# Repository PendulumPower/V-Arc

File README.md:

# V-ARC (WIP)
V-ARC is a multi-effects pedal, preamp, ble page turner, and looper designed for electric violin. It can also be used for other electric
instruments such as guitar. It runs on 2 separate controllers and includes a Lipo battery. It will be capable of being wirelessly reprogrammed for convienience,
and should have an app later in development so that settings can be tweaked or effects swapped without interacting with it. It is also going to feature MIDI conversion
and wireless playback in the future.
<br>Images:
<br>Schematic:

<br>PCB:

<br>Cost Breakdown:
<br>-Digikey components+Tax+Tariff+Shipping: ~$80
<br>Dasiy seed3+Tax+Shipping: ~$40
<br>PCB+Stencil+Tax+Shipping: ~$35
<br>Total: ~$155

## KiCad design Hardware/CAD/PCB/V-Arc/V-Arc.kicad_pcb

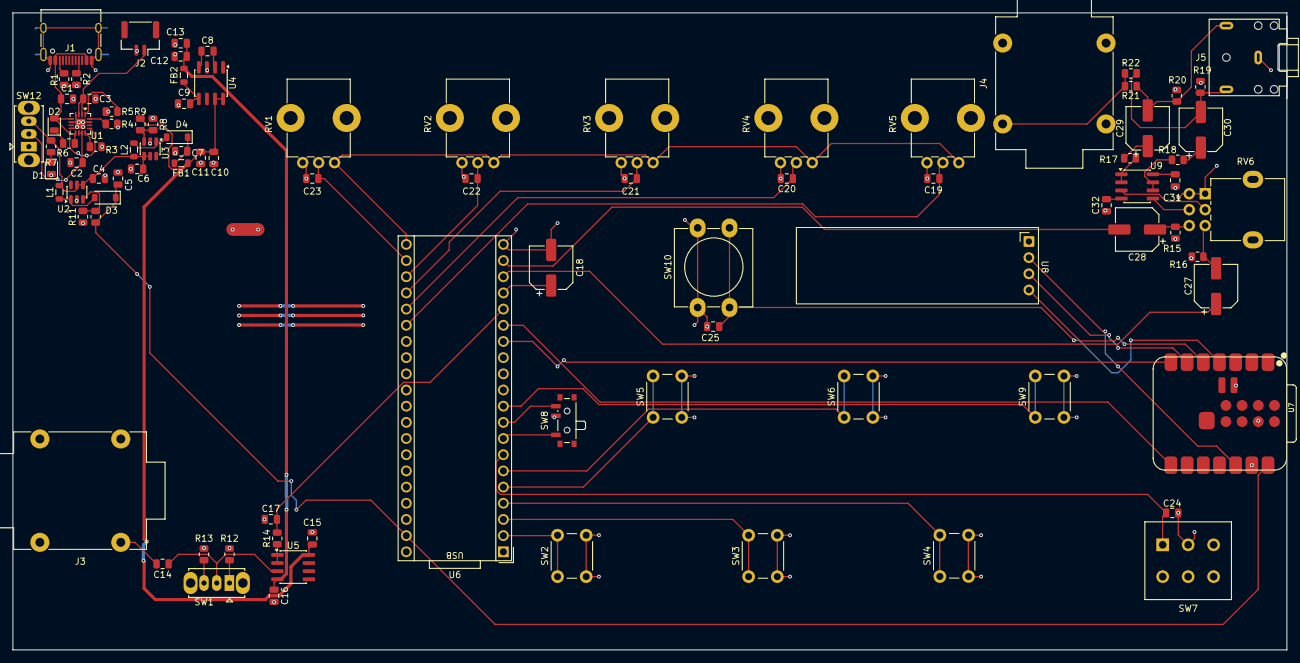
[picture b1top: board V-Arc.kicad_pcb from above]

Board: 2 copper layers, 200.0 x 100.0 mm, 93 parts (0 on the bottom side), 68 nets.

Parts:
C1: 1 µF; C_0805_2012Metric
C2, C3, C4, C6, C8, C9, C10, C12: 10 µF; C_0805_2012Metric
C5, C7: 22 µF; C_0805_2012Metric
C11, C13: .1 µF; C_0805_2012Metric
C14, C15, C16, C31, C32: 0.1 µF; C_0805_2012Metric
C17: 2.2 nF; C_0805_2012Metric
C18, C27, C28, C29, C30: 10 µF; CP_Elec_6.3x5.4
C19, C20, C21, C22, C23, C24: 100 nF; C_0805_2012Metric
C25: 10 nF; C_0805_2012Metric
D1, D2: LED_Small; LED_0805_2012Metric
D3, D4: D_Schottky; D_SOD-123
FB1, FB2: FerriteBead; L_0805_2012Metric
J1: USB_C_Receptacle_USB2.0_16P; USB_C_Receptacle_HRO_TYPE-C-31-M-12
J2: Conn_01x02; JST_GH_SM02B-GHS-TB_1x02-1MP_P1.25mm_Horizontal
J3: AudioJack2_SwitchT; Jack_6.35mm_Neutrik_NMJ4HCD2_Horizontal
J4: AudioJack2; Jack_6.35mm_Neutrik_NMJ4HCD2_Horizontal
J5: AudioJack3; Jack_3.5mm_CUI_SJ1-3523N_Horizontal
L1, L2: 4.7 µH; L_0805_2012Metric
NT1: NetTie_2; NetTie-2_SMD_Pad2.0mm
R1, R2: 5.1 kΩ; R_0805_2012Metric
R3: 1.5 kΩ; R_0805_2012Metric
R4: 1.8 kΩ; R_0805_2012Metric
R5, R8, R11, R21, R22: 10 kΩ; R_0805_2012Metric
R6, R7, R14: 1 kΩ; R_0805_2012Metric
R9: 140 kΩ; R_0805_2012Metric
R10: 75 kΩ; R_0805_2012Metric
R12: 1 MΩ; R_0805_2012Metric
R13: 10 MΩ; R_0805_2012Metric
R15, R16, R19, R20: 100 kΩ; R_0805_2012Metric
R17, R18: 100 Ω; R_0805_2012Metric
RV1, RV2, RV3, RV4, RV5: 10 kΩ; Potentiometer_Bourns_PTV09A-1_Single_Vertical
RV6: 10 kΩ; Potentiometer_Alpha_RD902F-40-00D_Dual_Vertical
SW1, SW12: SW_SPDT; SW_Slide_SPDT_Straight_CK_OS102011MS2Q
SW2, SW3, SW4, SW5, SW6, SW9: SW_SPDT; SW_PUSH_6mm
SW7: SW_Push; SW_PUSH_E-Switch_FS5700DP_DPDT
SW8: SW_SPDT_MSM; SW_SPDT_PCM12
SW10: SW_Push; SW_PUSH-12mm_Wuerth-430476085716
U1: BQ24072RGT; VQFN-16-1EP_3x3mm_P0.5mm_EP1.6x1.6mm
U2, U3: MT3608; SOT-23-6
U4: MAX1044; SOIC-8_3.9x4.9mm_P1.27mm
U5, U9: TL072; SOIC-8_3.9x4.9mm_P1.27mm
U6: Daisy_Seed; DAISY_SEED
U7: XIAO-ESP32-S3-SMD
U8: ER_OLEDM0.91_1x-I2C

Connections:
/Analog Front End/+9V: C10.1, C11.1, C15.1, FB1.1, R9.2, U4.7 (OSC), U4.8 (V+), U5.8 (V+)
/Analog Front End/-9V: C12.1, C13.1, C16.1, FB2.2, U5.4 (V-)
/Analog Front End/AUDIO_IN_ANALOG: C17.2, R14.2, U6.16 (AUDIO_IN_1)
/Daisy Seed Core/+3.3V: RV1.1, RV2.1, RV3.1, RV4.1, RV5.1, U6.21 (3V3_A)
/Daisy Seed Core/+5V: C5.2, D3.1 (K), R10.2, U6.39 (VIN), U7.14 (VBUS)
/Daisy Seed Core/AUDIO_OUT_ANALOG_L: C27.1, U6.18 (AUDIO_OUT_1)
/Daisy Seed Core/AUDIO_OUT_ANALOG_R: C28.2, U6.19 (AUDIO_OUT_2)
/Daisy Seed Core/DSP_UART_RX: U6.15 (D14), U7.8 (D7)
/Daisy Seed Core/DSP_UART_TX: U6.14 (D13), U7.7 (D6)
/Power Management/VBAT+: C3.2, J2.1, U1.2 (BAT), U1.3 (BAT)
/Power Management/VBUS: C1.1, D2.2 (A), J1.A4 (VBUS), J1.A9 (VBUS), J1.B4 (VBUS), J1.B9 (VBUS), U1.5 (EN2), U1.13 (IN)
/Power Management/VSYS: C4.1, C6.1, L1.1, L2.2, R7.2, SW12.3 (C), U2.4 (EN), U2.5 (IN), U3.4 (EN), U3.5 (IN)
/Xiao ESP Core/+9V: C31.1, U9.8 (V+)
/Xiao ESP Core/-9V: C32.1, U9.4 (V-)
/Xiao ESP Core/OUT_L_FINAL: C29.2, J5.T, R20.1, R21.2
/Xiao ESP Core/OUT_R_FINAL: C30.2, J5.R, R19.2, R22.2
/Xiao ESP Core/XiaoV: U7.12 (3V3_OUT), U8.2 (VCC)
GNDA: C15.2, C16.2, C17.1, C18.2, C19.1, C20.1, C21.1, C22.1, C23.1, C31.2, C32.2, J3.S, J3.TN, J4.S, J5.S, NT1.2, R12.2, R13.2, R15.2, R16.1, R19.1, R20.2, RV1.3, RV2.3, RV3.3, RV4.3, RV5.3, RV6.1, RV6.4, U6.20 (AGND)
GNDD: C1.2, C2.2, C3.1, C4.2, C5.1, C6.2, C7.1, C9.2, C10.2, C11.2, C12.2, C13.2, C24.1, C25.1, D1.1 (K), J1.A1 (GND), J1.A12 (GND), J1.B1 (GND), J1.B12 (GND), J1.SH (SHIELD), J2.2, NT1.1, R1.2, R2.2, R3.2, R4.1, R5.1, R8.1, R11.1, SW2.2 (B), SW3.2 (B), SW4.2 (B), SW5.2 (B), SW6.2 (B), SW7.2, SW8.2 (3), SW9.2 (B), SW10.1, U1.4 (~CE), U1.6 (EN1), U1.8 (VSS), U1.15 (TD), U1.17 (VSS), U2.2 (GND), U3.2 (GND), U4.3 (GND), U6.40 (DGND), U7.13 (GND), U7.18 (GND), U7.24 (GND), U8.1 (GND)
unnamed: C14.2, J3.T
unnamed: C27.2, R16.2, RV6.3
unnamed: C28.1, R15.1, RV6.6
unnamed: C29.1, R17.2
unnamed: C30.1, R18.2
unnamed: D1.2 (A), R7.1
unnamed: D2.1 (K), R6.1
unnamed: D3.2 (A), L1.2, U2.1 (SW)
unnamed: D4.2 (A), L2.1, U3.1 (SW)
unnamed: C7.2, D4.1 (K), FB1.2
unnamed: J1.A5 (CC1), R2.1
unnamed: J1.B5 (CC2), R1.1
unnamed: J4.T, R21.1, R22.1
unnamed: R12.1, SW1.1 (A)
unnamed: C14.1, SW1.2 (B), U5.3 (+)
unnamed: R13.1, SW1.3 (C)
unnamed: SW2.1 (A), U6.2 (D1)
unnamed: SW3.1 (A), U6.3 (D2)
unnamed: SW4.1 (A), U6.4 (D3)
unnamed: SW5.1 (A), U6.5 (D4)
unnamed: SW6.1 (A), U6.6 (D5)
unnamed: SW8.3 (4), U6.9 (D8)
unnamed: SW9.1 (A), U6.10 (D9)
unnamed: C2.1, SW12.2 (B), U1.10 (OUT), U1.11 (OUT)
unnamed: R3.1, U1.12 (ILIM)
unnamed: R4.2, U1.16 (ISET)
unnamed: R5.2, U1.1 (TS)
unnamed: R6.2, U1.9 (~CHG)
unnamed: R10.1, R11.2, U2.3 (FB)
unnamed: R8.2, R9.1, U3.3 (FB)
unnamed: C8.2, U4.2 (CAP+)
unnamed: C8.1, U4.4 (CAP-)
unnamed: C9.1, FB2.1, U4.5 (VOUT)
unnamed: R14.1, U5.1, U5.2 (-)
unnamed: C18.1, U6.17 (AUDIO_IN_2)
unnamed: C24.2, SW7.1, U6.7 (D6)
unnamed: SW8.1, U6.8 (D7)
unnamed: C23.2, RV1.2, U6.22 (D15)
unnamed: C22.2, RV2.2, U6.23 (D16)
unnamed: C21.2, RV3.2, U6.24 (D17)
unnamed: C20.2, RV4.2, U6.25 (D18)
unnamed: C19.2, RV5.2, U6.26 (D19)
unnamed: C25.2, SW10.2, U7.4 (D3)
unnamed: U7.5 (D4), U8.4 (SDA)
unnamed: U7.6 (D5), U8.3 (SCL)
unnamed: RV6.2, U9.3 (+)
unnamed: R17.1, U9.1, U9.2 (-)
unnamed: RV6.5, U9.5 (+)
unnamed: R18.1, U9.6 (-), U9.7
